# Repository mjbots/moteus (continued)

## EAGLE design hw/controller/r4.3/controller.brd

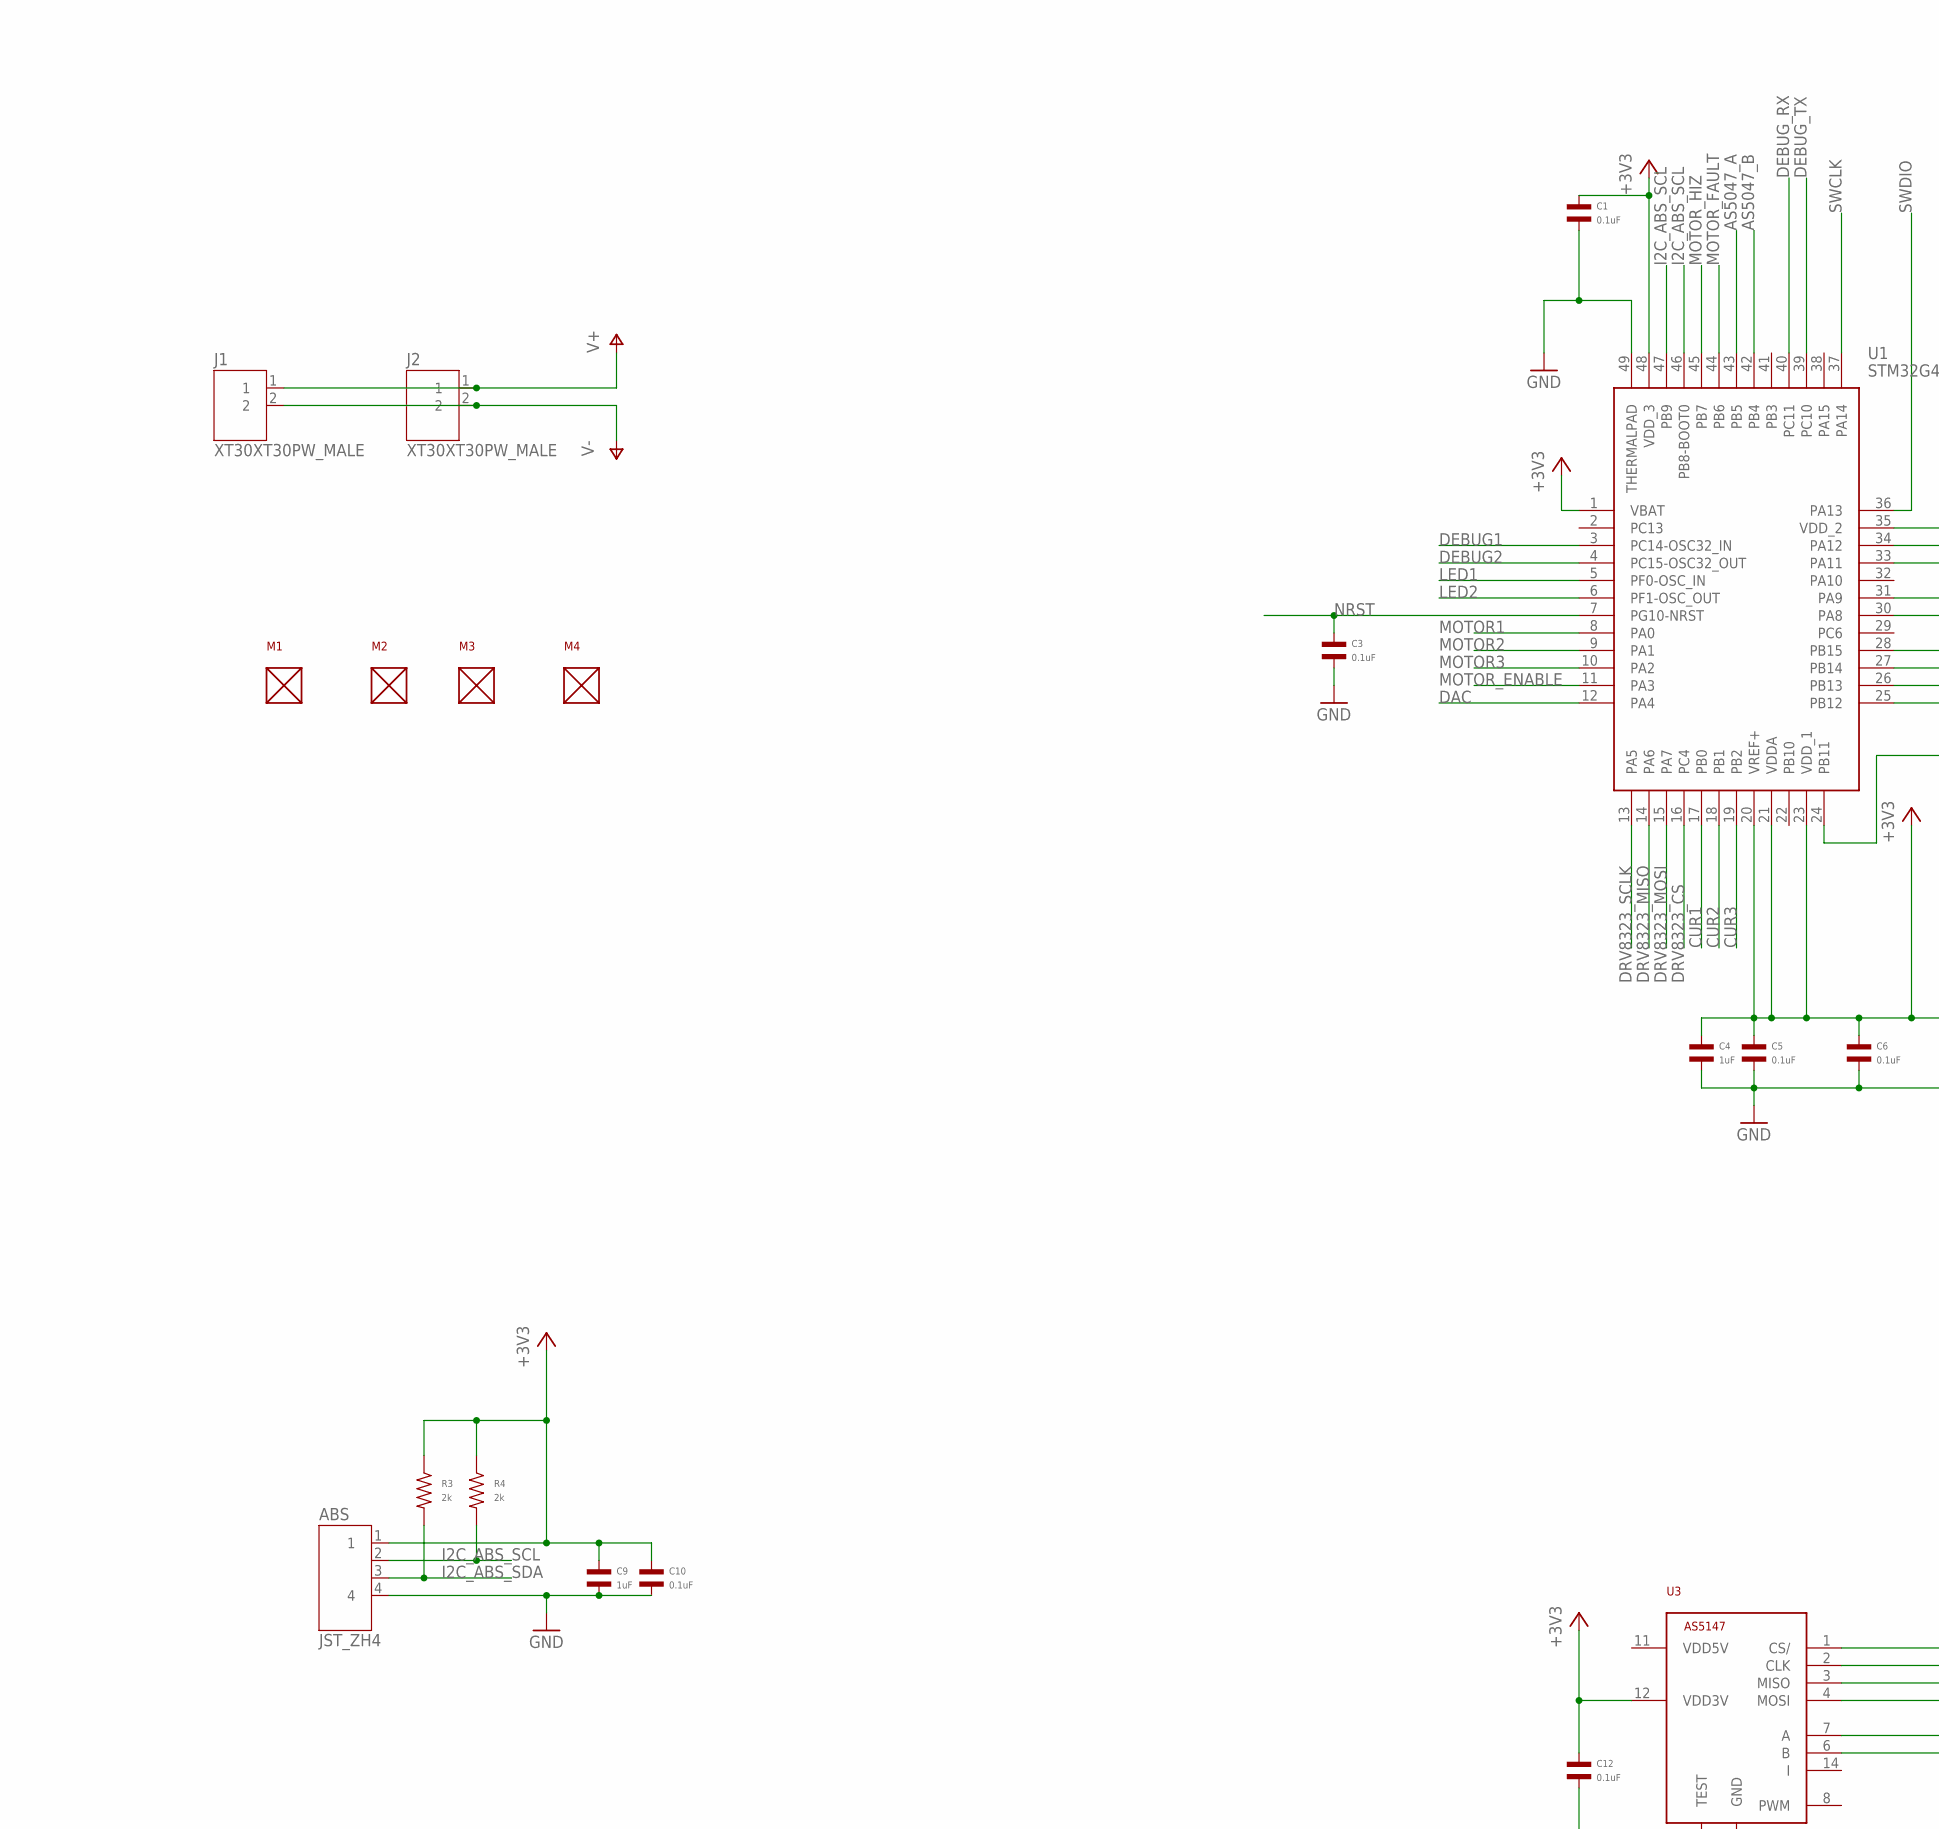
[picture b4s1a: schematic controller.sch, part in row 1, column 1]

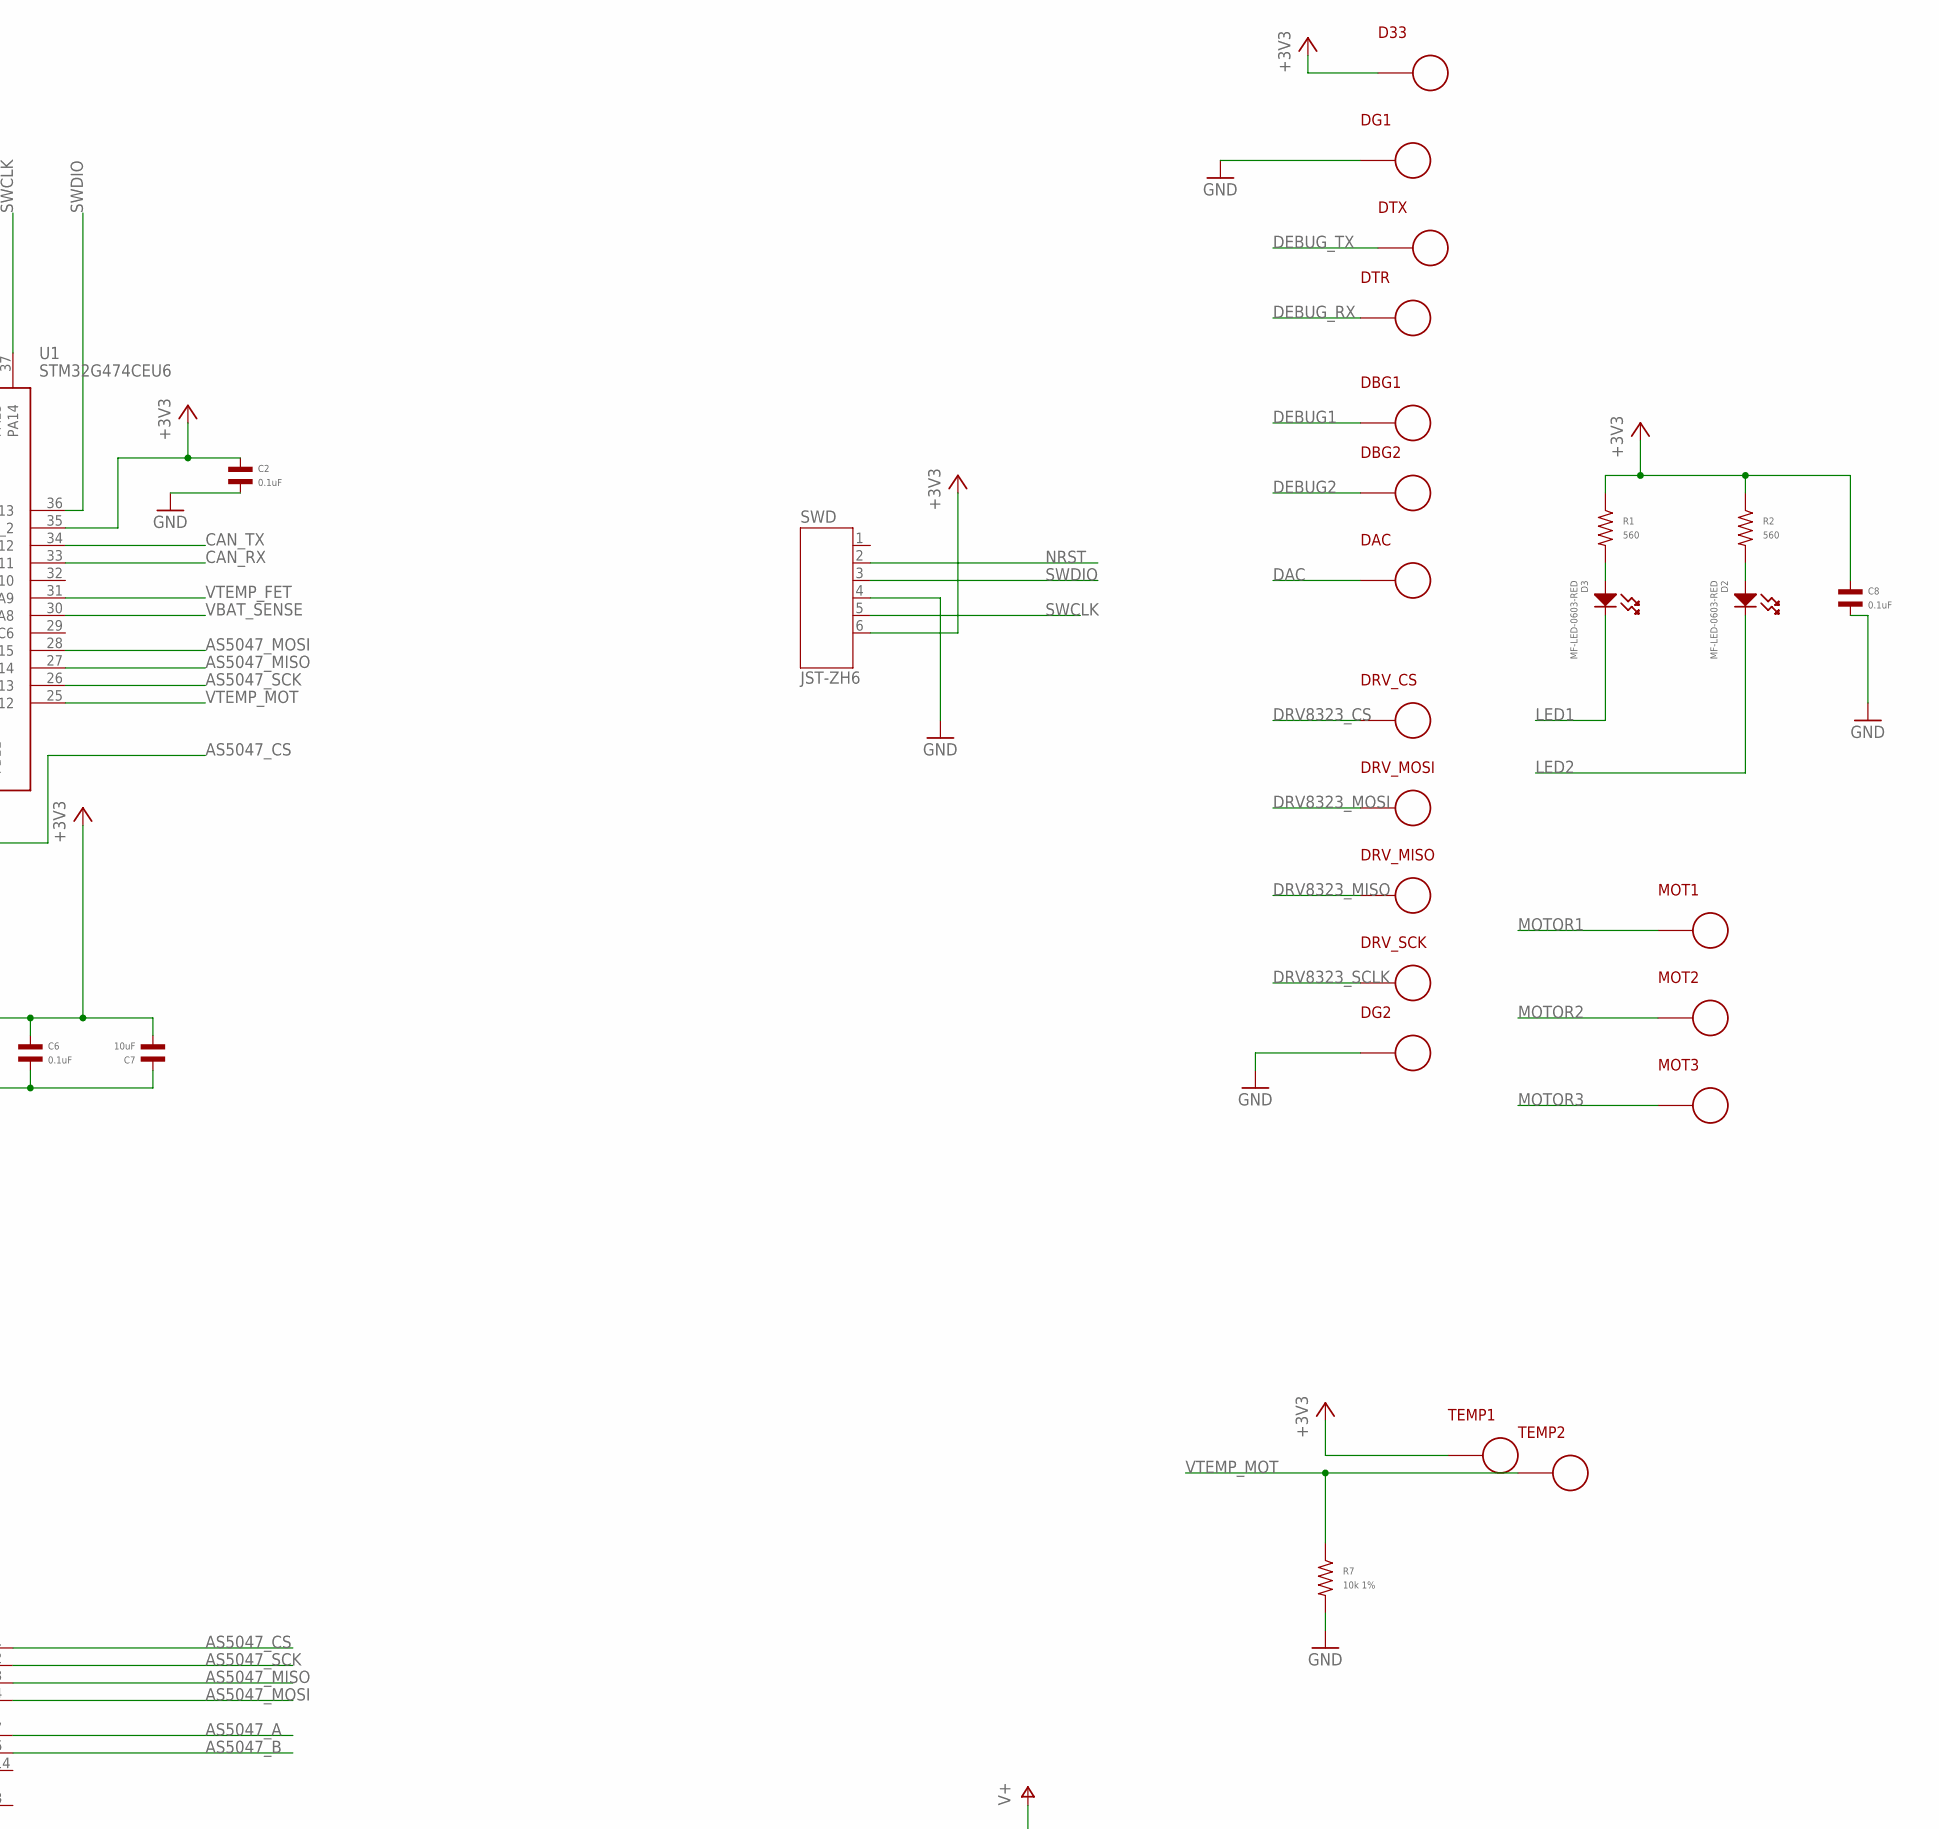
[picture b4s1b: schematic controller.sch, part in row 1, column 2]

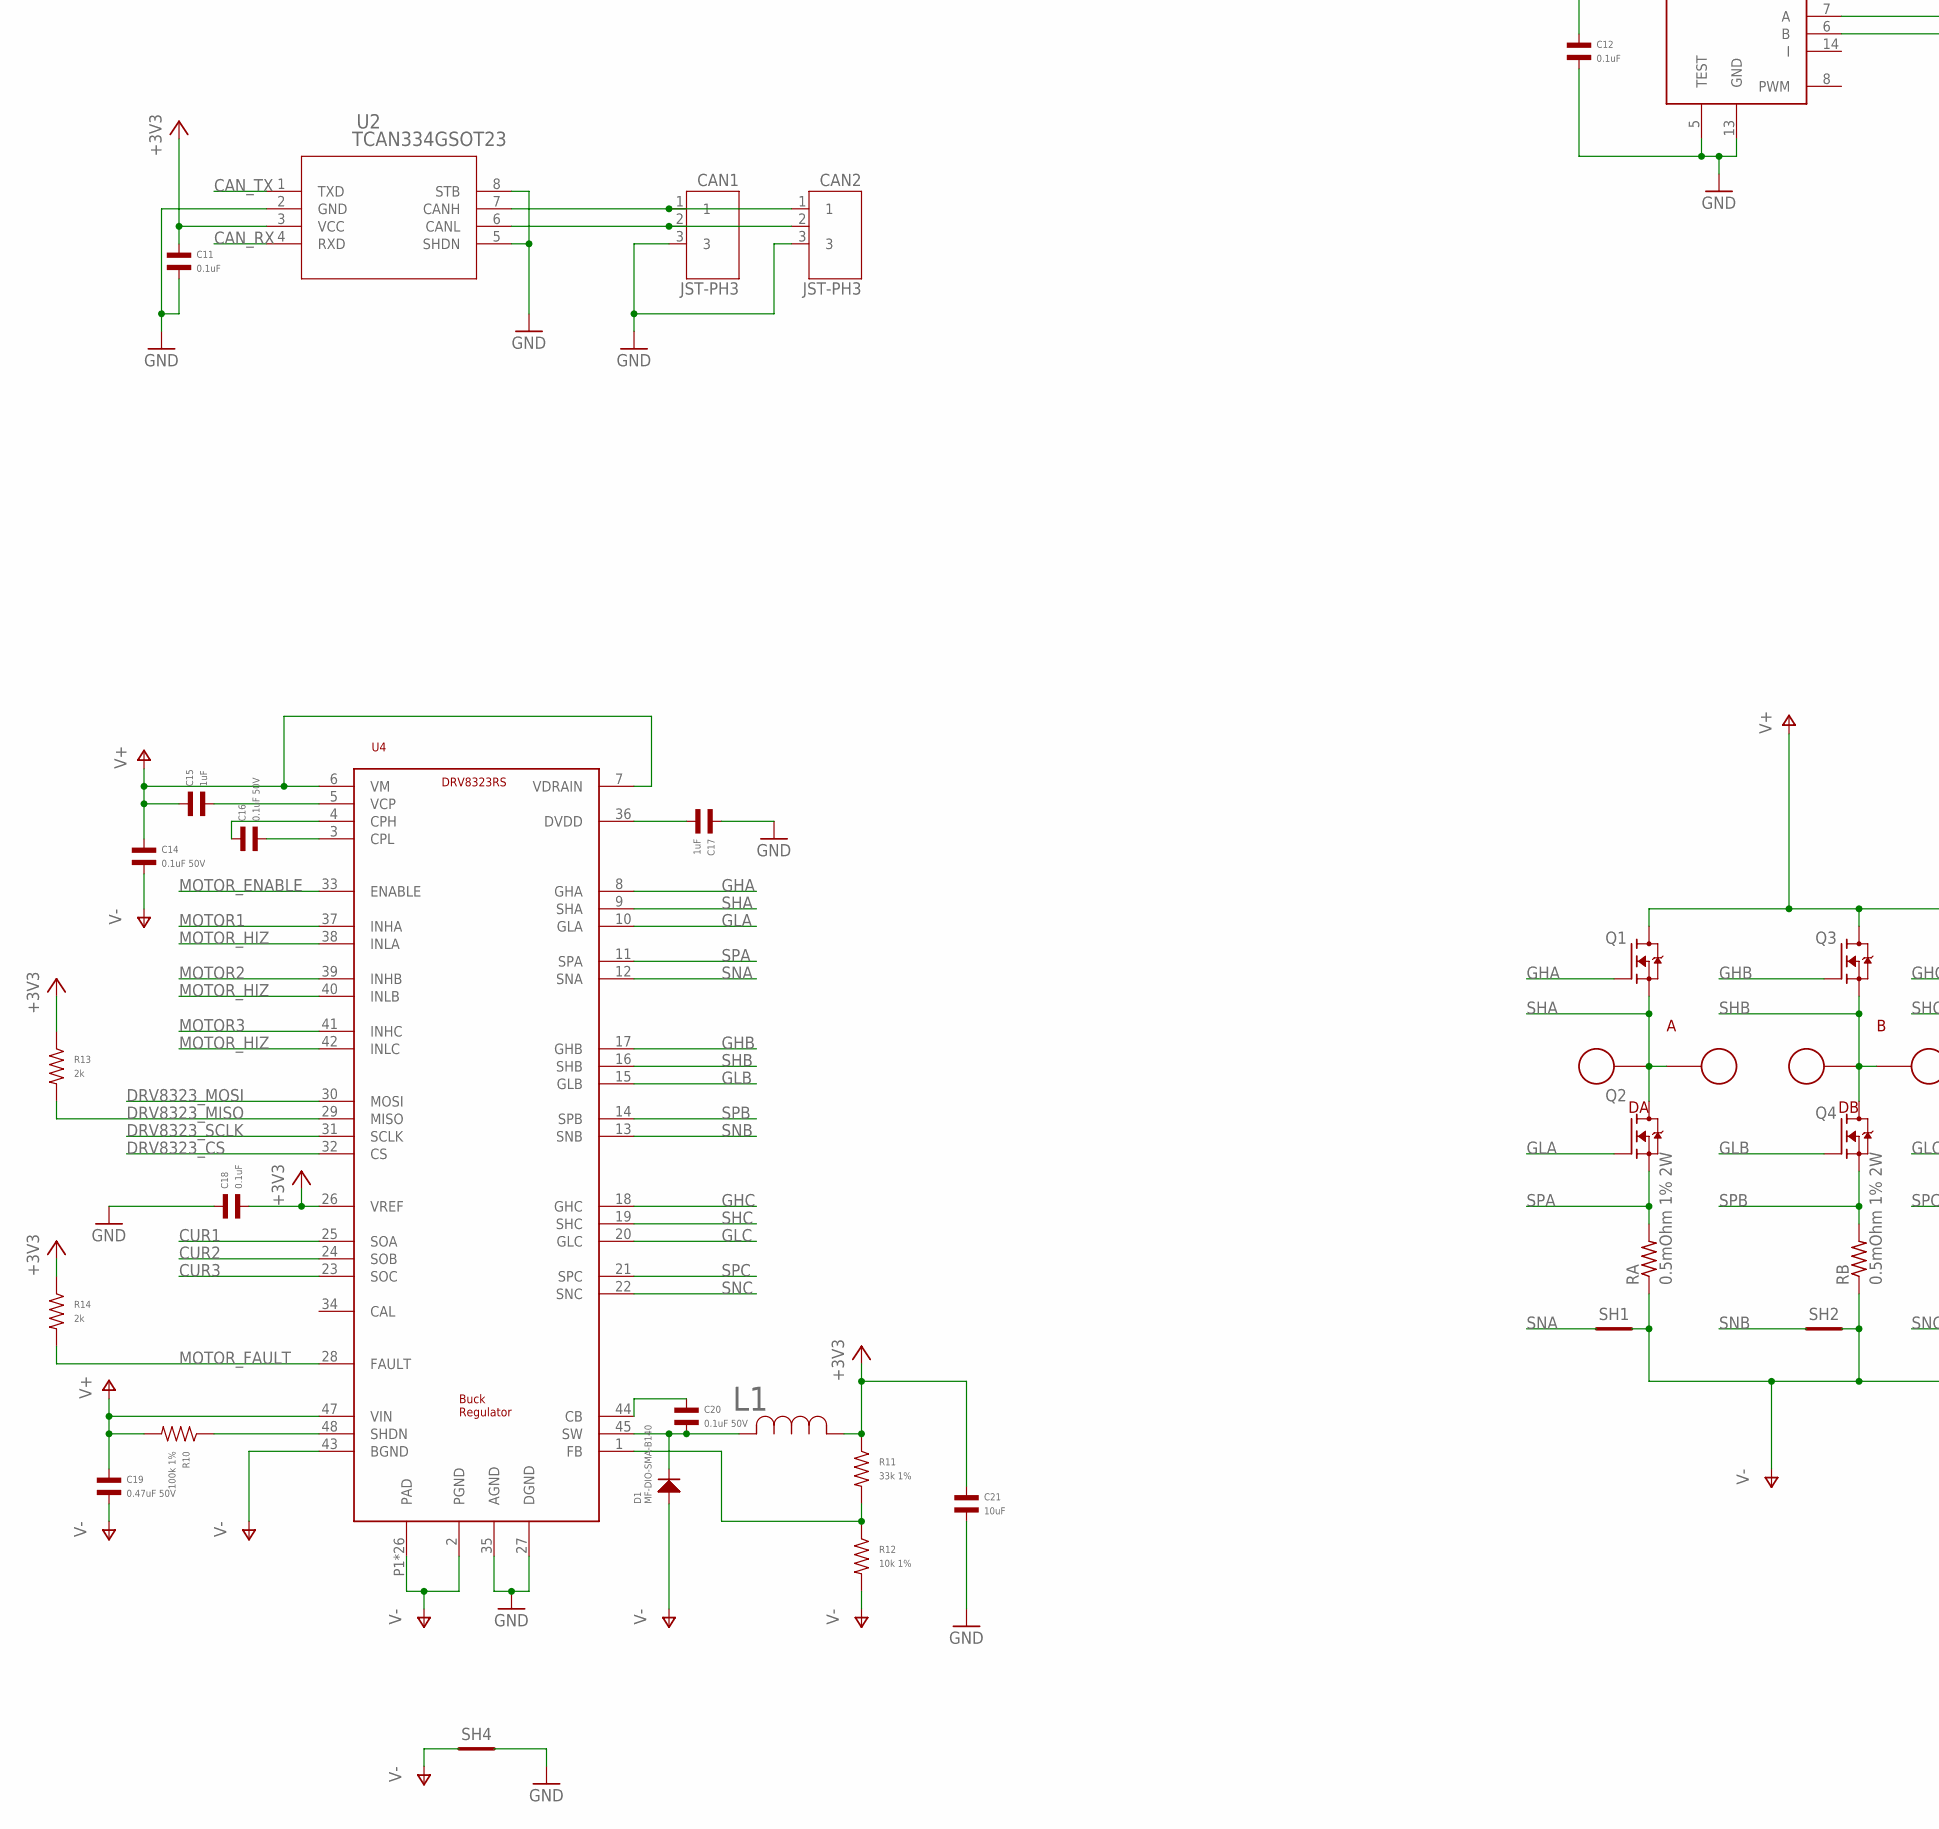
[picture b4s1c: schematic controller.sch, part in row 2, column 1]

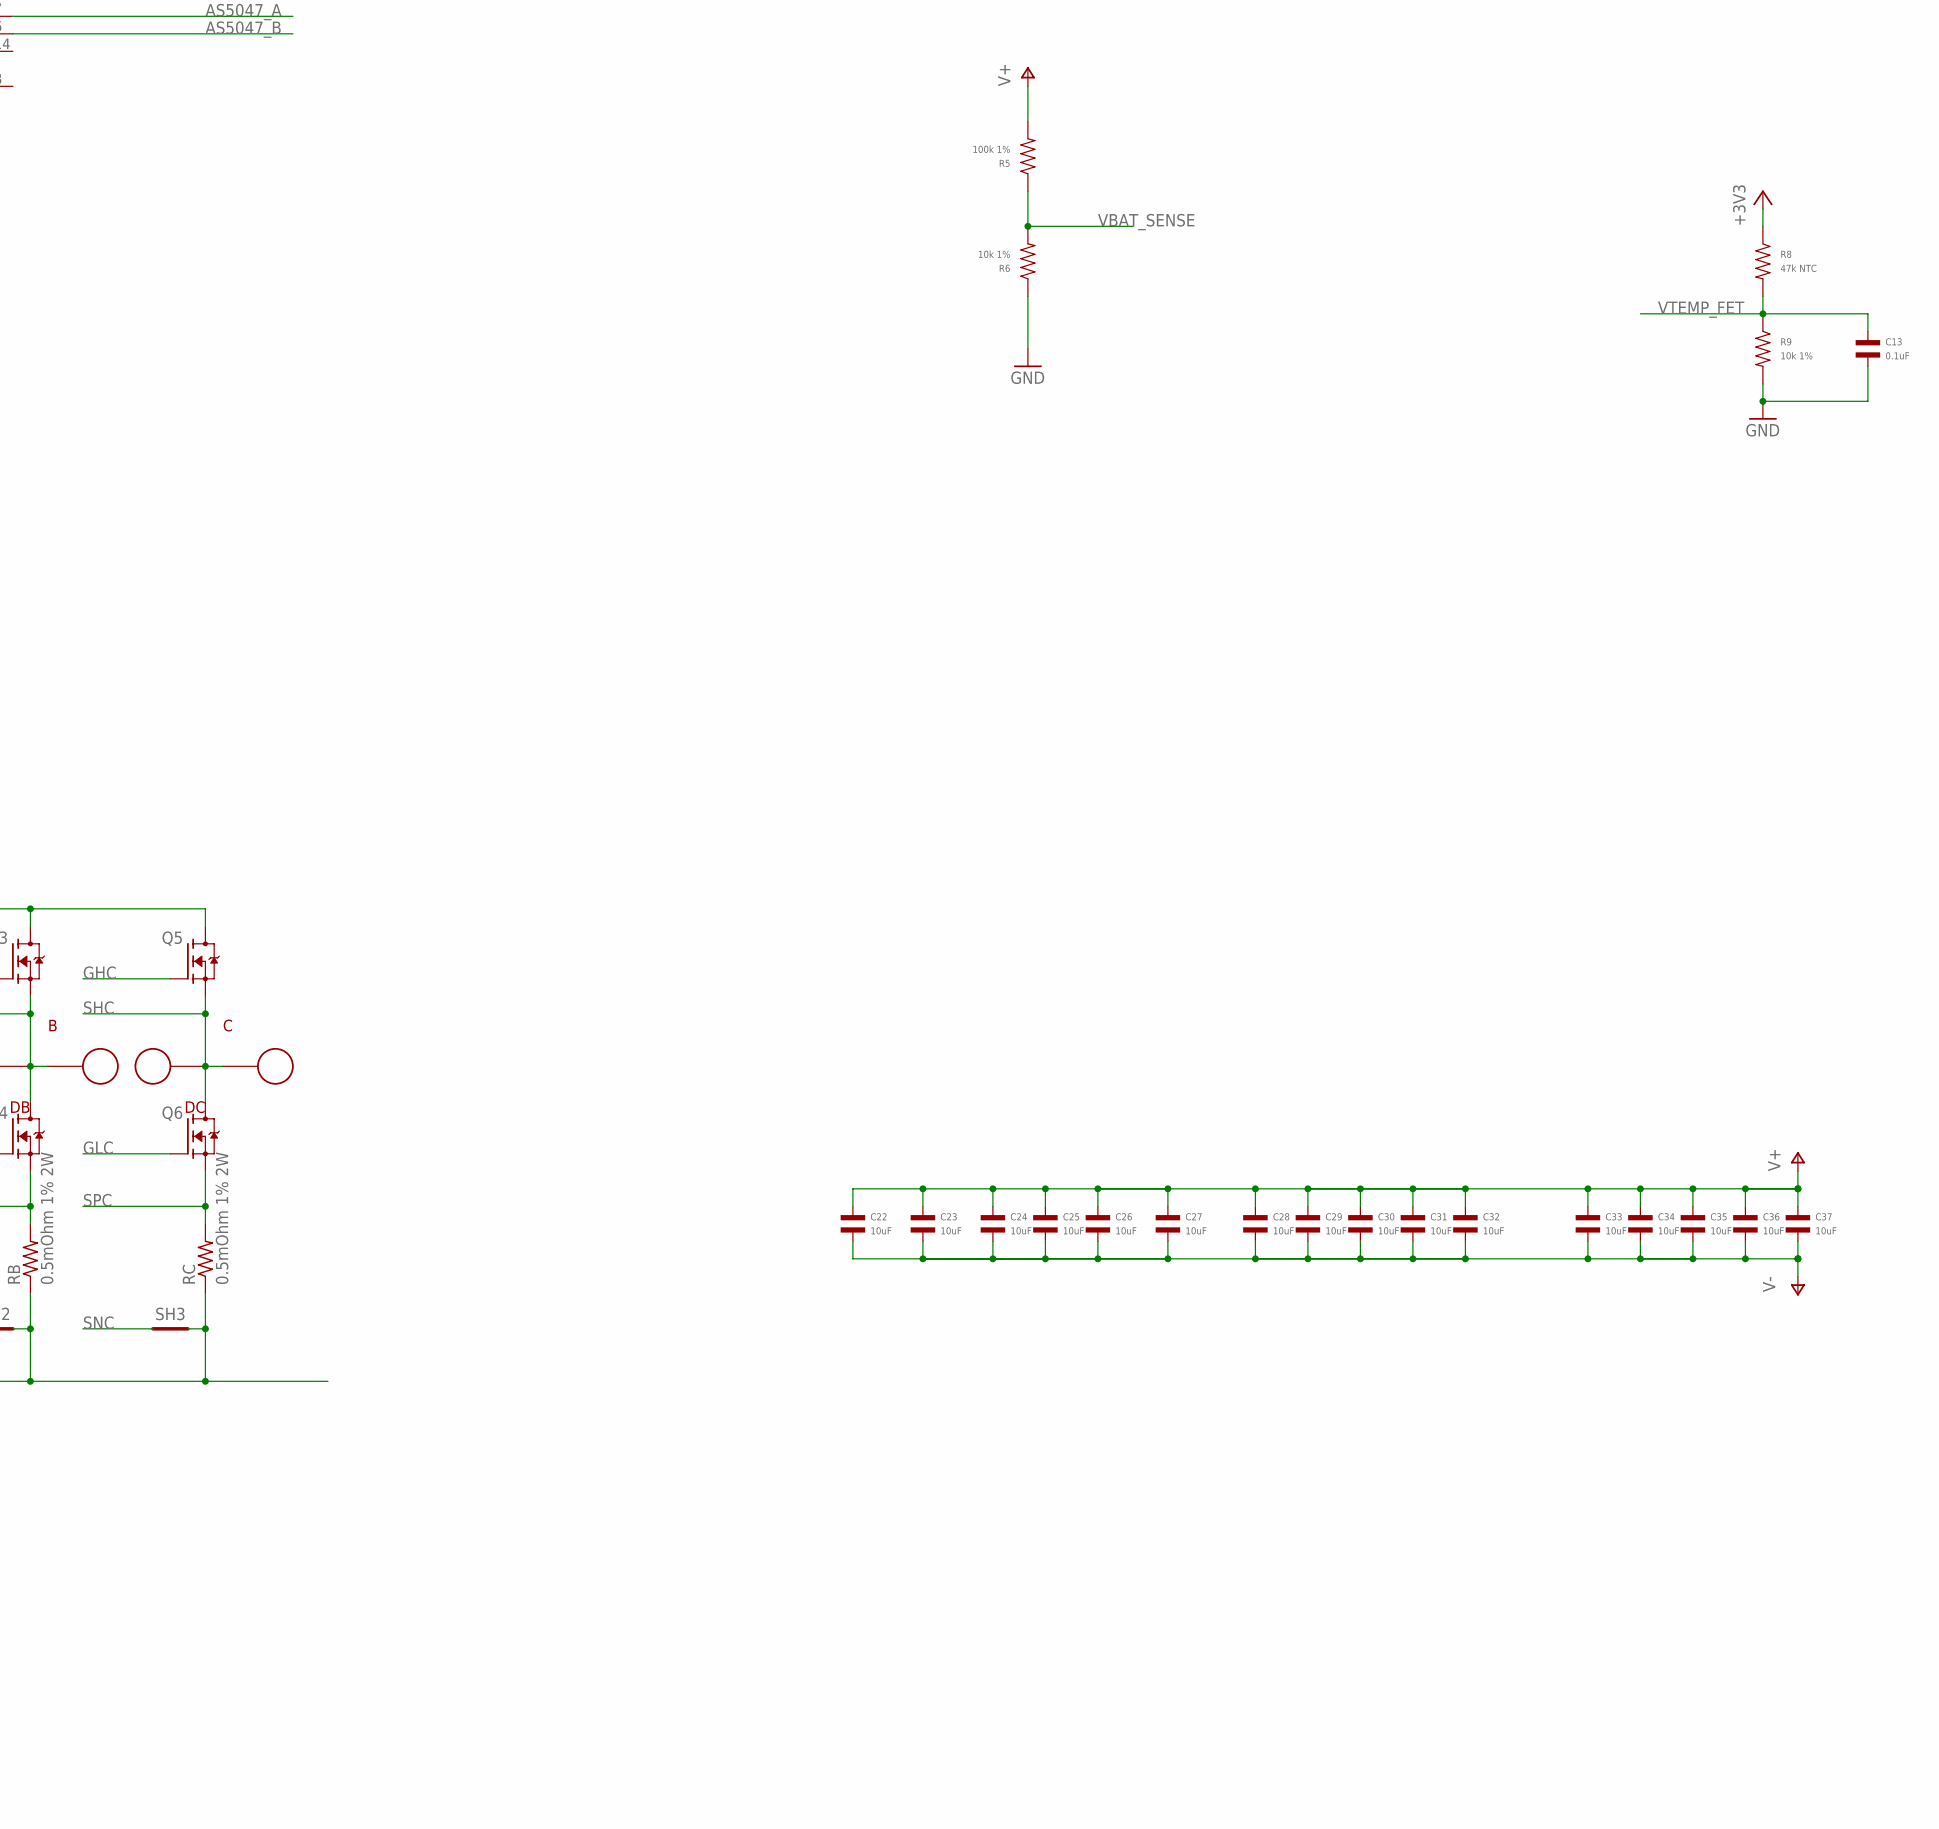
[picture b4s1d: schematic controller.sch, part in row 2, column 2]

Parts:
A: PAD; 18AWG_PAD
ABS: JST_ZH4; JST_S4B-ZR-SM4A-TF(LF)(SN); MPN S4B-ZR-SM4A-TF(LF)(SN)
B: PAD; 18AWG_PAD
C: PAD; 18AWG_PAD
C1, C2, C3, C5, C6, C8, C10, C11, C12, C13, C18: 0.1uF; C0402; MPN MF-CAP-0402-0.1uF
C4, C9, C15, C17: 1uF; C0402; MPN MF-CAP-0402-1uF
C7, C21: 10uF; C1206; MPN MF-CAP-1206-10uF
C14, C16, C20: 0.1uF 50V; C0402; MPN CGA2B3X7R1H104K050BB
C19: 0.47uF 50V; C0402; MPN UMK105ABJ474KV-F
C22, C23, C24, C25, C26, C27, C28, C29, C30, C31, C32, C33, C34, C35, C36, C37: 10uF; C1206; MPN CGA5L1X7R1H106K160AC
CAN1, CAN2: JST-PH3; JST_S3B-PH-SM4-TB(LF)(SN); MPN S3B-PH-SM4-TB(LF)(SN)
D1: MF-DIO-SMA-B140; SMA
D2: MF-LED-0603-RED; LED0603; MPN MF-LED-0603-GREEN
D3: MF-LED-0603-RED; LED0603
D33: PAD24AWG_PAD; 24AWG_PAD
DA: PAD24AWG_PAD; 24AWG_PAD
DAC: PAD24AWG_PAD; 24AWG_PAD
DB: PAD24AWG_PAD; 24AWG_PAD
DBG1, DBG2: PAD24AWG_PAD; 24AWG_PAD
DC: PAD24AWG_PAD; 24AWG_PAD
DG1, DG2: PAD24AWG_PAD; 24AWG_PAD
DRV_CS: PAD24AWG_PAD; 24AWG_PAD
DRV_MISO: PAD24AWG_PAD; 24AWG_PAD
DRV_MOSI: PAD24AWG_PAD; 24AWG_PAD
DRV_SCK: PAD24AWG_PAD; 24AWG_PAD
DTR: PAD24AWG_PAD; 24AWG_PAD
DTX: PAD24AWG_PAD; 24AWG_PAD
J1, J2: XT30XT30PW_MALE; XT30PW_MALE
L1: SRN4018-220M; IND_BOURNS_SRN4018; MPN SRN4018-220M
M1, M2, M3, M4: MOUNT; M2.5MOUNT
MOT1, MOT2, MOT3: PAD24AWG_PAD; 24AWG_PAD
Q1, Q2, Q3, Q4, Q5, Q6: TPH1R204PLSOP_ADVANCE_8; SOP_ADVANCE_8; MPN TPH1R204PL,L1Q
R1, R2: 560; R0402; MPN MF-RES-0402-560
R3, R4, R13, R14: 2k; R0402; MPN MF-RES-0402-2K
R5, R10: 100k 1%; R0402; MPN ERJ-2RKF1003X
R6, R7, R9, R12: 10k 1%; R0402; MPN ERJ-2RKF1002X
R8: 47k NTC; R0402; MPN NCP15WB473F03RC
R11: 33k 1%; R0402; MPN ERJ-2RKF3302X
RA: 0.5mOhm 1% 2W; M1206; MPN HCS1206FTL500
RB: 0.5mOhm 1% 2W; M1206; MPN HCS1206FTL500
RC: 0.5mOhm 1% 2W; M1206; MPN HCS1206FTL500
SH1, SH2, SH3: SHORTT5; SHORT_TOP-50
SH4: SHORTBIG; SHORT_TOP-BIG
SWD: JST-ZH6; JST_S6B-ZR-SM4A-TF(LF)(SN); MPN S6B-ZR-SM4A-TF(LF)(SN)
TEMP1, TEMP2: PAD24AWG_PAD; 24AWG_PAD
U1: STM32G474CEU6; QFN50P700X700X60-49N; MPN STM32G474CEU6
U2: TCAN334GSOT23; SOT23-8; MPN TCAN334GDCNT
U3: AS5147; TSSOP14; MPN AS5047P-ATSM
U4: DRV8323RS; PVQFN-N48; MPN DRV8323RSRGZR

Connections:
+3V3: ABS.1, C1.P$1, C2.P$1, C4.P$1, C5.P$1, C6.P$1, C7.P$2, C8.P$1, C9.P$1, C10.P$1, C11.P$1, C12.P$1, C18.P$2, C21.P$1, D33.P$1, L1.1, R1.P$1, R2.P$1, R3.P$1, R4.P$1, R8.P$1, R11.P$1, R13.P$1, R14.P$1, SWD.6, TEMP1.P$1, U1.1 (VBAT), U1.20 (VREF+), U1.21 (VDDA), U1.23 (VDD_1), U1.35 (VDD_2), U1.48 (VDD_3), U2.3 (VCC), U3.12 (VDD3V), U4.26 (VREF)
AS5047_A: U1.43 (PB5), U3.7 (A)
AS5047_B: U1.42 (PB4), U3.6 (B)
AS5047_CS: U1.24 (PB11), U3.1 (CS/)
AS5047_MISO: U1.27 (PB14), U3.3 (MISO)
AS5047_MOSI: U1.28 (PB15), U3.4 (MOSI)
AS5047_SCK: U1.26 (PB13), U3.2 (CLK)
CAN_N: CAN1.2, CAN2.2, U2.6 (CANL)
CAN_P: CAN1.1, CAN2.1, U2.7 (CANH)
CAN_RX: U1.33 (PA11), U2.4 (RXD)
CAN_TX: U1.34 (PA12), U2.1 (TXD)
CUR1: U1.17 (PB0), U4.25 (SOA)
CUR2: U1.18 (PB1), U4.24 (SOB)
CUR3: U1.19 (PB2), U4.23 (SOC)
DAC: DAC.P$1, U1.12 (PA4)
DEBUG1: DBG1.P$1, U1.3 (PC14-OSC32_IN)
DEBUG2: DBG2.P$1, U1.4 (PC15-OSC32_OUT)
DEBUG_RX: DTR.P$1, U1.40 (PC11)
DEBUG_TX: DTX.P$1, U1.39 (PC10)
DRV8323_CS: DRV_CS.P$1, U1.16 (PC4), U4.32 (CS)
DRV8323_MISO: DRV_MISO.P$1, R13.P$2, U1.14 (PA6), U4.29 (MISO)
DRV8323_MOSI: DRV_MOSI.P$1, U1.15 (PA7), U4.30 (MOSI)
DRV8323_SCLK: DRV_SCK.P$1, U1.13 (PA5), U4.31 (SCLK)
GHA: Q1.4 (G), U4.8 (GHA)
GHB: Q3.4 (G), U4.17 (GHB)
GHC: Q5.4 (G), U4.18 (GHC)
GLA: Q2.4 (G), U4.10 (GLA)
GLB: Q4.4 (G), U4.15 (GLB)
GLC: Q6.4 (G), U4.20 (GLC)
GND: ABS.4, C1.P$2, C2.P$2, C3.P$2, C4.P$2, C5.P$2, C6.P$2, C7.P$1, C8.P$2, C9.P$2, C10.P$2, C11.P$2, C12.P$2, C13.P$2, C17.P$1, C18.P$1, C21.P$2, CAN1.3, CAN2.3, DG1.P$1, DG2.P$1, R6.P$1, R7.P$2, R9.P$2, SH4.2, SWD.4, U1.49 (THERMALPAD), U2.2 (GND), U2.5 (SHDN), U2.8 (STB), U3.5 (TEST), U3.13 (GND), U4.27 (DGND), U4.35 (AGND)
I2C_ABS_SCL: ABS.2, R4.P$2, U1.46 (PB8-BOOT0), U1.47 (PB9)
I2C_ABS_SDA: ABS.3, R3.P$2
LED1: D3.CATHODE, U1.5 (PF0-OSC_IN)
LED2: D2.CATHODE, U1.6 (PF1-OSC_OUT)
MOTOR1: MOT1.P$1, U1.8 (PA0), U4.37 (INHA)
MOTOR2: MOT2.P$1, U1.9 (PA1), U4.39 (INHB)
MOTOR3: MOT3.P$1, U1.10 (PA2), U4.41 (INHC)
MOTOR_ENABLE: U1.11 (PA3), U4.33 (ENABLE)
MOTOR_FAULT: R14.P$2, U1.44 (PB6), U4.28 (FAULT)
MOTOR_HIZ: U1.45 (PB7), U4.38 (INLA), U4.40 (INLB), U4.42 (INLC)
unnamed: R10.P$1, U4.48 (SHDN)
unnamed: R11.P$2, R12.P$1, U4.1 (FB)
unnamed: C16.P$2, U4.3 (CPL)
unnamed: C20.P$2, D1.CATHODE, L1.2, U4.45 (SW)
unnamed: C20.P$1, U4.44 (CB)
unnamed: C16.P$1, U4.4 (CPH)
unnamed: C15.P$2, U4.5 (VCP)
unnamed: C17.P$2, U4.36 (DVDD)
unnamed: D3.ANODE, R1.P$2
unnamed: D2.ANODE, R2.P$2
NRST: C3.P$1, SWD.2, U1.7 (PG10-NRST)
SHA: A.1, DA.P$1, Q1.1 (S), Q1.2 (S), Q1.3 (S), Q2.5 (D), Q2.6 (D), Q2.7 (D), Q2.8 (D), Q2.PAD (D), U4.9 (SHA)
SHB: B.1, DB.P$1, Q3.1 (S), Q3.2 (S), Q3.3 (S), Q4.5 (D), Q4.6 (D), Q4.7 (D), Q4.8 (D), Q4.PAD (D), U4.16 (SHB)
SHC: C.1, DC.P$1, Q5.1 (S), Q5.2 (S), Q5.3 (S), Q6.5 (D), Q6.6 (D), Q6.7 (D), Q6.8 (D), Q6.PAD (D), U4.19 (SHC)
SNA: SH1.1, U4.12 (SNA)
SNB: SH2.1, U4.13 (SNB)
SNC: SH3.1, U4.22 (SNC)
SPA: Q2.1 (S), Q2.2 (S), Q2.3 (S), RA.2, U4.11 (SPA)
SPB: Q4.1 (S), Q4.2 (S), Q4.3 (S), RB.2, U4.14 (SPB)
SPC: Q6.1 (S), Q6.2 (S), Q6.3 (S), RC.2, U4.21 (SPC)
SWCLK: SWD.5, U1.37 (PA14)
SWDIO: SWD.3, U1.36 (PA13)
V+: C14.P$1, C15.P$1, C19.P$1, C22.P$1, C23.P$1, C24.P$1, C25.P$1, C26.P$1, C27.P$1, C28.P$1, C29.P$1, C30.P$1, C31.P$1, C32.P$1, C33.P$1, C34.P$1, C35.P$1, C36.P$1, C37.P$1, J1.1, J2.1, Q1.5 (D), Q1.6 (D), Q1.7 (D), Q1.8 (D), Q1.PAD (D), Q3.5 (D), Q3.6 (D), Q3.7 (D), Q3.8 (D), Q3.PAD (D), Q5.5 (D), Q5.6 (D), Q5.7 (D), Q5.8 (D), Q5.PAD (D), R5.P$2, R10.P$2, U4.6 (VM), U4.7 (VDRAIN), U4.47 (VIN)
V-: C14.P$2, C19.P$2, C22.P$2, C23.P$2, C24.P$2, C25.P$2, C26.P$2, C27.P$2, C28.P$2, C29.P$2, C30.P$2, C31.P$2, C32.P$2, C33.P$2, C34.P$2, C35.P$2, C36.P$2, C37.P$2, D1.ANODE, J1.2, J2.2, R12.P$2, RA.1, RB.1, RC.1, SH1.2, SH2.2, SH3.2, SH4.1, U4.2 (PGND), U4.43 (BGND), U4.P1 (PAD), U4.P2 (PAD), U4.P3 (PAD), U4.P4 (PAD), U4.P5 (PAD), U4.P6 (PAD), U4.P7 (PAD), U4.P8 (PAD), U4.P9 (PAD), U4.P10 (PAD), U4.P11 (PAD), U4.P12 (PAD), U4.P13 (PAD), U4.P14 (PAD), U4.P15 (PAD), U4.P16 (PAD), U4.P17 (PAD), U4.P18 (PAD), U4.P19 (PAD), U4.P20 (PAD), U4.P21 (PAD), U4.P22 (PAD), U4.P23 (PAD), U4.P24 (PAD), U4.P25 (PAD), U4.PAD
VBAT_SENSE: R5.P$1, R6.P$2, U1.30 (PA8)
VTEMP_FET: C13.P$1, R8.P$2, R9.P$1, U1.31 (PA9)
VTEMP_MOT: R7.P$1, TEMP2.P$1, U1.25 (PB12)

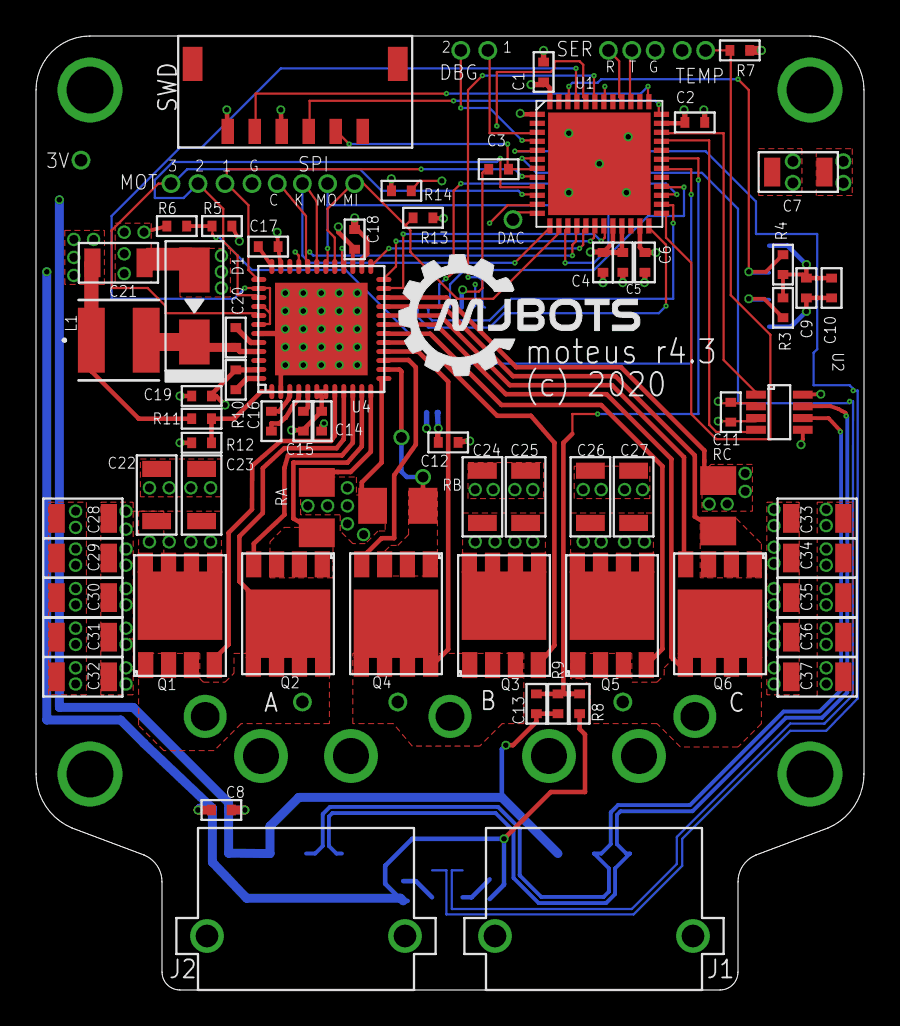
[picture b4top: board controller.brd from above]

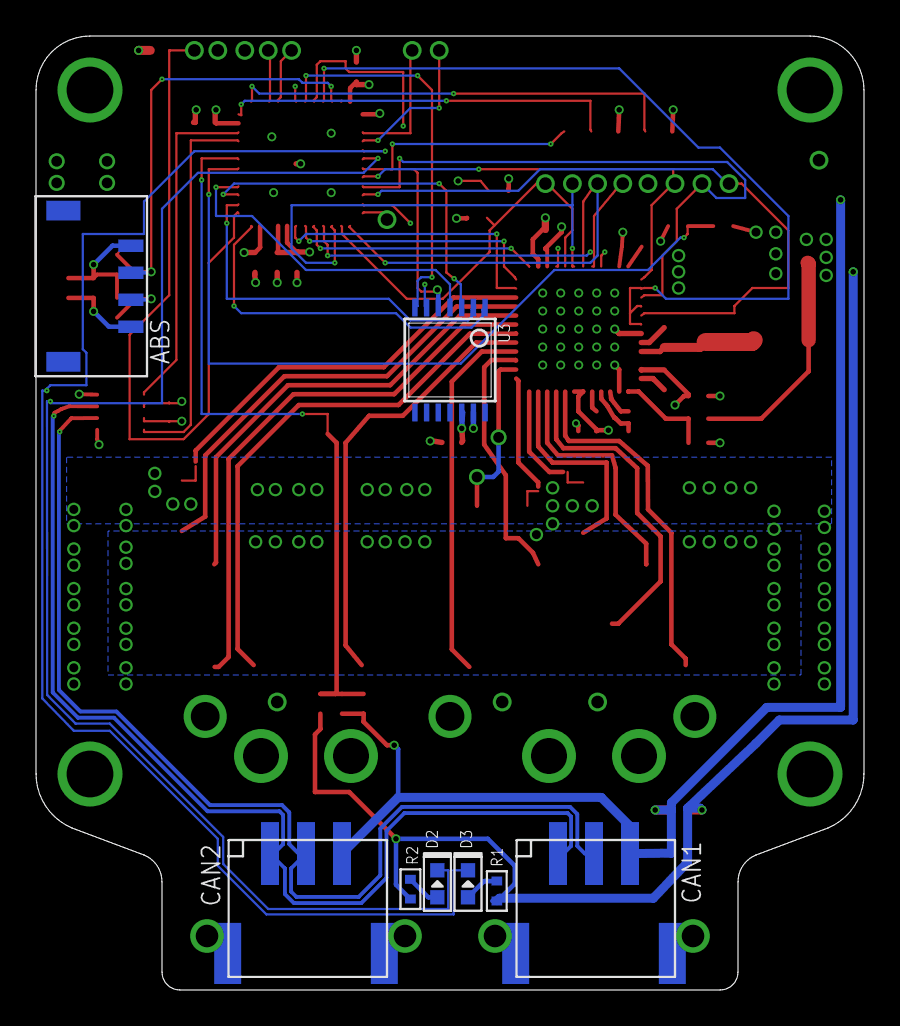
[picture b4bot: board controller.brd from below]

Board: 4 copper layers, 46.0 x 53.0 mm, 105 parts (8 on the bottom side), 67 nets.

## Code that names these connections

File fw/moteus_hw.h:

// Copyright 2023 mjbots Robotic Systems, LLC.  info@mjbots.com
//
// Licensed under the Apache License, Version 2.0 (the "License");
// you may not use this file except in compliance with the License.
// You may obtain a copy of the License at
//
//     http://www.apache.org/licenses/LICENSE-2.0
//
// Unless required by applicable law or agreed to in writing, software
// distributed under the License is distributed on an "AS IS" BASIS,
// WITHOUT WARRANTIES OR CONDITIONS OF ANY KIND, either express or implied.
// See the License for the specific language governing permissions and
// limitations under the License.

#pragma once

#include "mbed.h"

#include "fw/fet_thermal_model.h"
#include "fw/millisecond_timer.h"

namespace moteus {

//////////////////////////////////////////
// The following "families" are supported:
//  moteus-r4 - family 0
//  moteus-n1 - family 1
//  moteus-c1 - family 2
//  moteus-x1 - family 3
//  moteus-r5 - family 4
//
// Each family has an independent hardware version timeline, and
// possibly a different mechanism for verifying hardware version
// compatibility.


// This structure is filled in once the family and hardware version
// are known.
struct MoteusHwPins {
  PinName pwm1 = PA_0_ALT0;
  PinName pwm2 = PA_1_ALT0;
  PinName pwm3 = PA_2_ALT0;

  PinName drv8323_enable = NC;
  PinName drv8323_hiz = NC;
  PinName drv8323_cs = NC;

  PinName drv8323_mosi = NC;
  PinName drv8323_miso = NC;
  PinName drv8323_sck = NC;
  PinName drv8323_fault = NC;

  PinName debug_led1 = NC;
  PinName power_led = NC;

  PinName current1 = NC;
  PinName current2 = NC;
  PinName current3 = NC;

  PinName vsense = NC;
  PinName tsense = PA_9;

  PinName msense = NC;

  float vsense_adc_scale = 0.0f;

  PinName as5047_cs = NC;

  PinName can_td = NC;
  PinName can_rd = NC;

  PinName debug1 = NC;
  PinName debug2 = NC;
  PinName debug_dac = PA_4;

  uint32_t model_number = 0;

  uint32_t firmware_version = 0x000105;

  // Each board has a power limit curve, below a bus voltage V_l, the
  // P_l power limit is used.  Above bus voltage V_h, P_h power limit
  // is used.  Between, the power limit is linearly interpolated.  All
  // power limits are normalized to 30kHz PWM.
  float power_P_l_W = 0.0f;
  float power_V_l = 24.0f;
  float power_P_h_W = 0.0f;
  float power_V_h = 34.0f;

  // Constants for the FET junction temperature estimator.  Every
  // board must provide these.  See fw/fet_thermal_model.h.
  FetThermalParams fet_thermal;
};


struct FamilyAndVersion {
  int family = 0;
  int hw_version = 0;
  int hw_pins = 0;
};

// Return what family we are executing on.
FamilyAndVersion DetectMoteusFamily(MillisecondTimer*);

MoteusHwPins FindHardwarePins(FamilyAndVersion);


// The "FIRMWARE_VERSION" is a misnomer.  It instead is the equivalent
// of an ABI version, and is incremented when configuration values
// change in a way that would not result in equivalent behavior across
// an upgrade/downgrade.

// Version history:

// # 0x0101 #
//
// * Fixed the calculation of feedforward voltage to have the correct
//   sign for the velocity component.  Previous firmwares,
//   inappropriately applied a negative feedforward term, which
//   counteracted rotation instead of being an actual feedforward.

// # 0x0102 #
//
// * Removed servo.feedforward_scale entirely

// # 0x0103 #
//
// * Added servo.pwm_scale, and for r4.8 boards changed the default
//   value of pwm_comp_off / pwm_comp_mag.

// # 0x0104 #
//
// * Added configurable PWM rates, which changed default values of
//   pwm_comp_mag and pwm_comp_off.

// # 0x0105 #
//
// * Switched to a new encoder and position subsystem.

// # 0x0106 #
//
// * Switched aux?.sources.x.i2c.poll_ms to poll_rate_us to match UART
//   and give more resolution.

// # 0x0107 #
//
// * Fixed motor_position.output.sign == -1 so that DQ commands for
//   voltage or current are inverted, so that positive Q axis voltage
//   or current results in positive speed

// # 0x0108 #
//
// * The default value of `servo.bemf_feedforward` was changed from
//   1.0 to 0.0.

// # 0x0109 #
//
// * Commutation compensation now interpolates, which means old tables
//   need to be upgraded during the flash process.
// * The motor thermistor value is now configurable and defaults to
//   10k instead of 47k.

// # 0x010a #
//
// * servo.max_power_W now defaults to NaN, and if present is used as
//   an absolute value rather than as a "nominal" value.

// # 0x010b #
//
// * servo.flux_brake_margin_voltage replaces
//   servo.flux_brake_min_voltage
// * servo.temperature_margin replaces servo.derate_temperature
// * servo.motor_temperature_margin replaces
//   servo.motor_derate_temperature

// # 0x010c #
//
// * motor_position.sources.x.pll_filter_hz was previously specified
//   in terms of a somewhat arbitrary "natural frequency", but is now
//   specified in terms of the 3dB cutoff frequency

// # 0x010d #
//
// * aux?.rs422 replaced aux?.uart.rs422 as now the RS422 transceiver
//   can be enabled for both UART and BiSS-C encoders

// # 0x010e #
//
// * servo.pid_dq.kp/ki/max_desired_rate replaced by servo.pid_dq_hz
//   and servo.max_current_desired_rate.  PI gains are now computed
//   automatically from the bandwidth and motor parameters.

// # 0x010000
//
// No functional changes.  ABI release 1.0.0

// # 0x010100
//
// * The drv8323_conf reg4 calculation now maps idriven_ls_ma through the
//   DRV8353 pull-down (idriven) table instead of the pull-up (idrivep)
//   table.  DRV8353-board idriven_ls_ma defaults were adjusted and
//   moteus_tool migrates stored configs so the gate-drive register
//   output is unchanged across the upgrade.
// * The gate-driver family routing was corrected: moteus-c1 (family 2,
//   a DRV8323) now uses the drv8323 register path and moteus-n1
//   (family 1, a DRV8353) uses the drv8353 register path.  These were
//   swapped by an inadvertent "family == 1" clause in the c1-support
//   commit.  c1's defaults are adjusted (and configs migrated) to keep
//   its register output unchanged; n1's register output is restored to
//   what it was before the c1-support commit.
//
// ABI release 1.1.0

#define MOTEUS_MODEL_NUMBER 0x0000
#define MOTEUS_FIRMWARE_VERSION 0x010100

extern MoteusHwPins g_hw_pins;

// Ensure the DRV8323 is turned off.
void MoteusEnsureOff();

}
